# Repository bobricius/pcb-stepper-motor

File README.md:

# pcb-stepper-motor

Hardware licensed under CERN OHL 1.2

Documentation licensed under CC-BY 4.0

PCB stepper motor
... is designed for direct drive wheels for swarm robots

Coils are etched on 4 layer PCB, about 40turns for one coil (8coils).

PROJECT PAGE

https://hackaday.io/project/85502-pcb-stepper-motor

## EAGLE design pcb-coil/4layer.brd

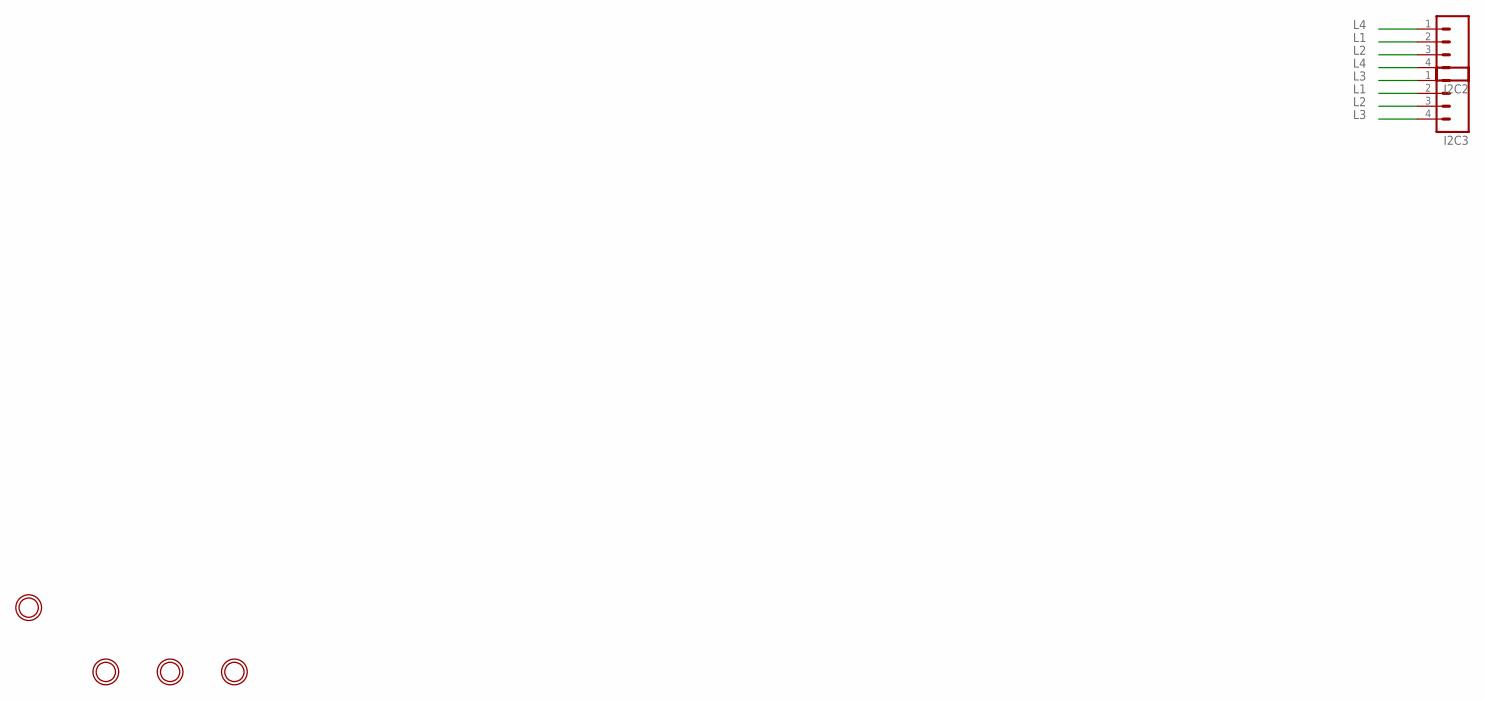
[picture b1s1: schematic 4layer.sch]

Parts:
I2C2, I2C3: M04PTH; 1X04
U$1, U$2, U$3, U$7: MOUNTINGHOLE2.0; MOUNTINGHOLE_2.0_PLATED

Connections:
L1: I2C2.2, I2C3.2
L2: I2C2.3, I2C3.3
L3: I2C3.1, I2C3.4
L4: I2C2.1, I2C2.4

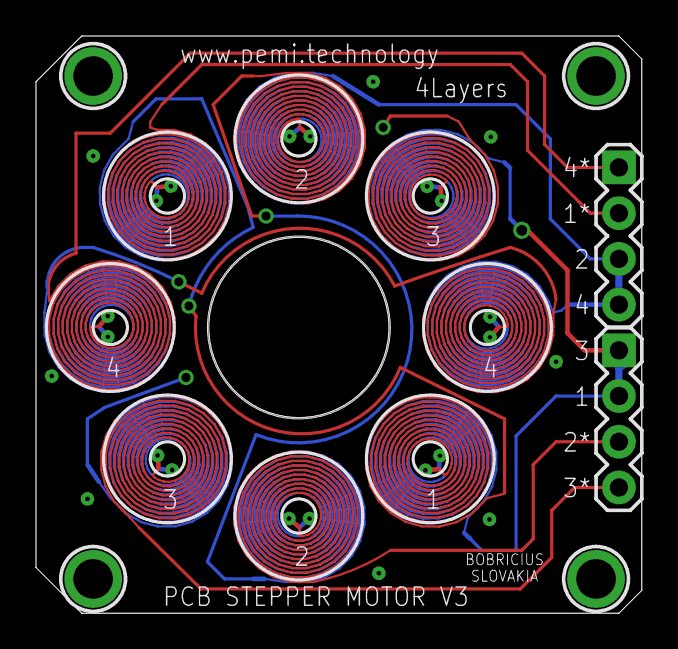
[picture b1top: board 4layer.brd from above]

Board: 4 copper layers, 33.6 x 32.0 mm, 6 parts (0 on the bottom side), 4 nets.

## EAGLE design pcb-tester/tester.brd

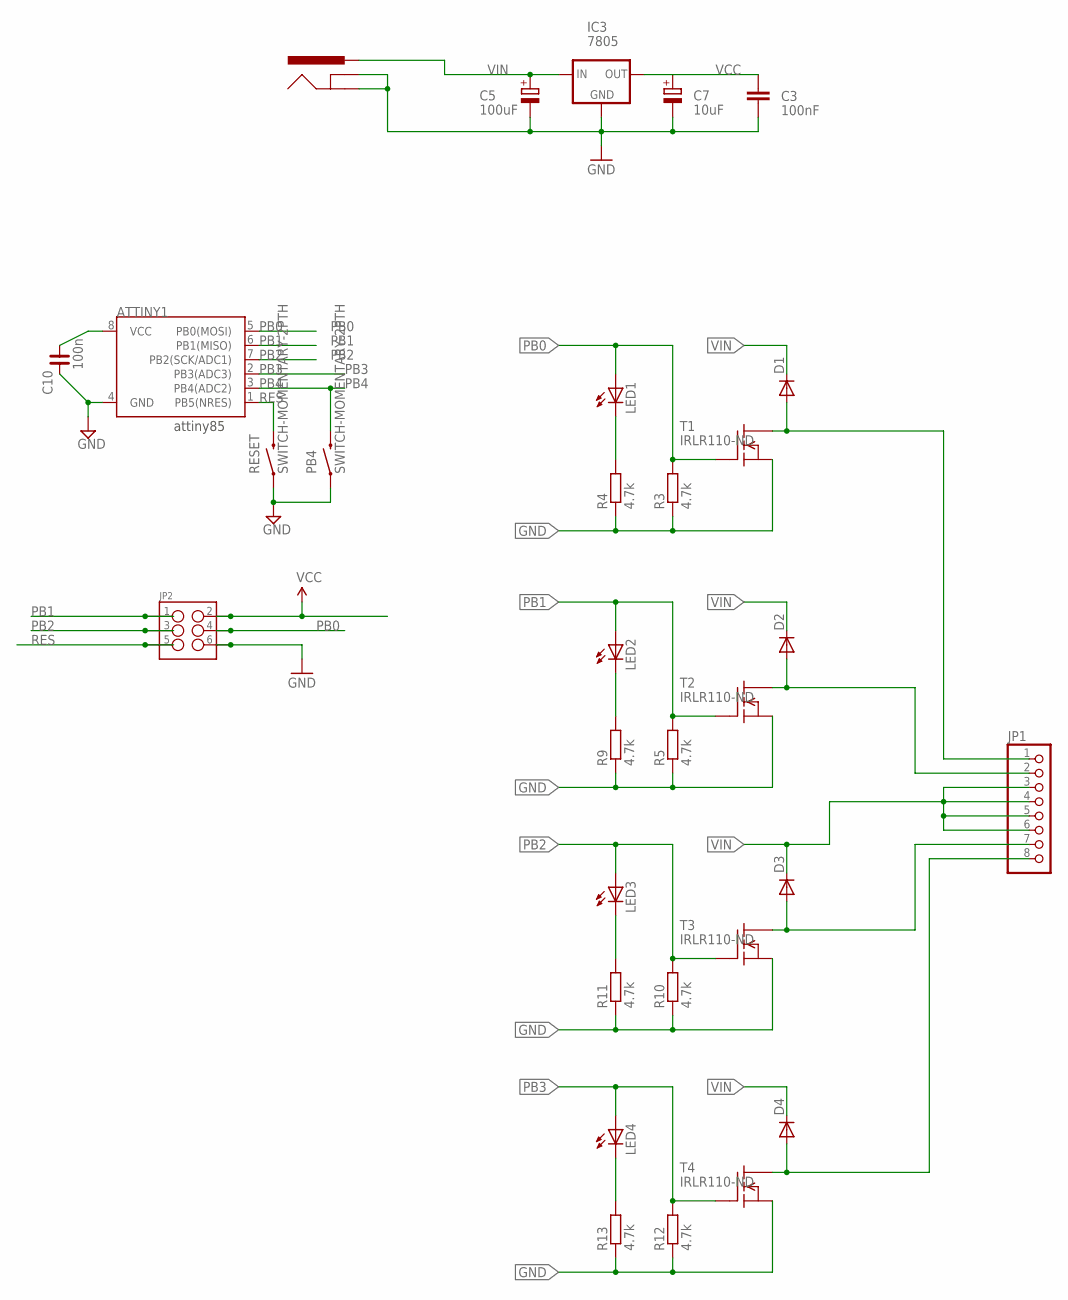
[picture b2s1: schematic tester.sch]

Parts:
ATTINY1: ATTINY45DIP8; DIP08
C3: 100nF; C050-024X044
C5: 100uF; E2,5-5
C7: 10uF; E2,5-5
C10: 100n; C0603
D1, D2, D3, D4: DIODE-DO214AC; DO214AC
IC3: 7805; 78XXL
J16: POWER_JACKPTH; POWER_JACK_PTH
JP1: PINHD-1X8; 1X08
JP2: M03X2NO_SILK; 2X3-NS@1
LED1, LED2, LED3, LED4: LEDCHIPLED_1206; CHIPLED_1206
PB4: SWITCH-MOMENTARY-2PTH; TACTILE-PTH
R3, R4, R5, R9, R10, R11, R12, R13: 4.7k; R0603
RESET: SWITCH-MOMENTARY-2PTH; TACTILE-PTH
T1, T2, T3, T4: IRLR110-ND; TO252

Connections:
GND: ATTINY1.4 (GND), C3.2, C5.-, C7.-, C10.2, IC3.GND, J16.GND, J16.GNDBREAK, JP2.6, PB4.1, R3.1, R4.1, R5.1, R9.1, R10.1, R11.1, R12.1, R13.1, RESET.1, T1.2 (S), T2.2 (S), T3.2 (S), T4.2 (S)
unnamed: LED1.C, R4.2
unnamed: D2.A, JP1.2, T2.3 (D)
unnamed: D1.A, JP1.1, T1.3 (D)
unnamed: D3.A, JP1.7, T3.3 (D)
unnamed: LED2.C, R9.2
unnamed: D4.A, JP1.8, T4.3 (D)
unnamed: LED3.C, R11.2
unnamed: LED4.C, R13.2
PB0: ATTINY1.5 (PB0(MOSI)), JP2.4, LED1.A, R3.2, T1.1 (G)
PB1: ATTINY1.6 (PB1(MISO)), JP2.1, LED2.A, R5.2, T2.1 (G)
PB2: ATTINY1.7 (PB2(SCK/ADC1)), JP2.3, LED3.A, R10.2, T3.1 (G)
PB3: ATTINY1.2 (PB3(ADC3)), LED4.A, R12.2, T4.1 (G)
PB4: ATTINY1.3 (PB4(ADC2)), PB4.3 (2)
RES: ATTINY1.1 (PB5(NRES)), JP2.5, RESET.3 (2)
VCC: ATTINY1.8 (VCC), C3.1, C7.+, C10.1, IC3.OUT, JP2.2
VIN: C5.+, D1.C, D2.C, D3.C, D4.C, IC3.IN, J16.PWR, JP1.3, JP1.4, JP1.5, JP1.6

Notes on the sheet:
attiny85

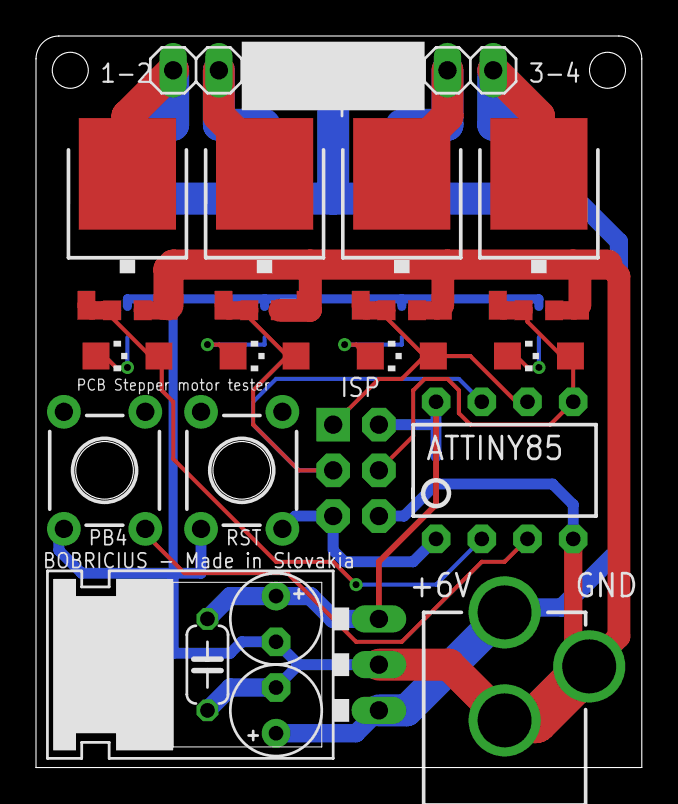
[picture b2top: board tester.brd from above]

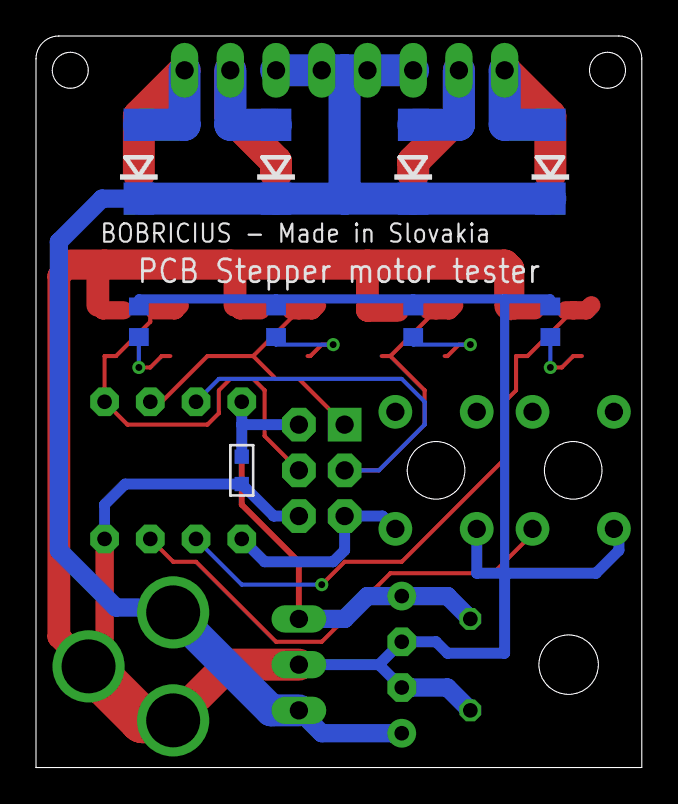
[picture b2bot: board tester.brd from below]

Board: 2 copper layers, 33.7 x 40.6 mm, 31 parts (9 on the bottom side), 17 nets.

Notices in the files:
parts and their libraries:
SparkFun-Connectors: Licensing: Creative Commons ShareAlike 4.0 International - https://creativecommons.org/licenses/by-sa/4.0
